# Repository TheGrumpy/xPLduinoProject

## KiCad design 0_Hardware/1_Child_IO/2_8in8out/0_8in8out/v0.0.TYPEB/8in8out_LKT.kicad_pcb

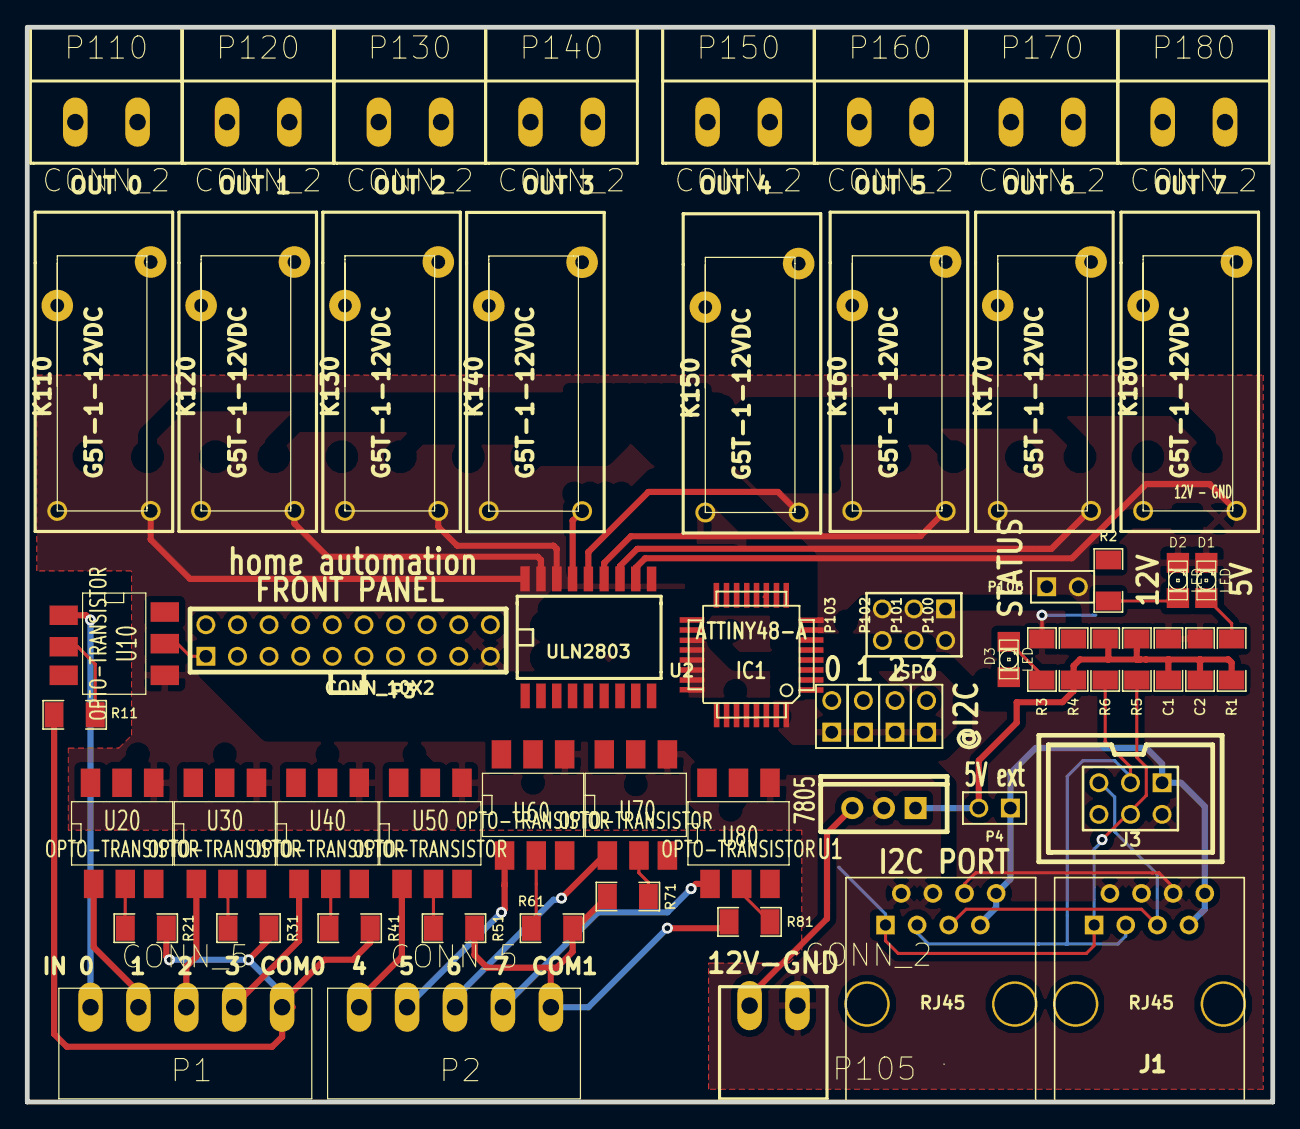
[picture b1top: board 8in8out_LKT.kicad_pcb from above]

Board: 2 copper layers, 100.1 x 86.4 mm, 60 parts (0 on the bottom side), 77 nets.

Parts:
C1, C2: C; SM1206
D1, D2, D3: LED; LED-1206
IC1: ATTINY48-A; TQFP32
ISP0: CONN_3X2; pin_array_3x2
J1, J2: RJ45; RJ45_8
J3: CONN_6; HE10-6
K110, K120, K130, K140, K150, K160, K170, K180: G5T-1-12VDC; LK-T
P1, P2: CONN_5; MOL_CONN_5_MINI
P3: CONN_10X2; pin_array_10x2
P4, P100, P101, P102, P103, P106: CONN_2; PIN_ARRAY_2X1
P105: CONN_2; MOL_CONN_2_MINI
P110, P120, P130, P140, P150, P160, P170, P180: CONN_2; MOL_CONN_2_VH
R1, R3, R11, R21, R31, R41, R51, R61, R71, R81: 2KR; SM1206
R2: 4.7KR; SM1206
R4, R5, R6: 10KR; SM1206
U1: 7805; TO220_7805_VERT
U2: ULN2803; SOIC18
U10, U20, U30, U40, U50, U60, U70, U80: OPTO-TRANSISTOR; CMS-6

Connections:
5V_EXT: J1.7, J1.8, J2.7, J2.8, J3.1, P4.1
+5V: C1.1, C2.1, IC1.4, IC1.18, ISP0.6, P3.20, P4.2, R1.1, R4.1, R5.1, R6.1, U1.VO
+12V: K110.1, K120.1, K130.1, K140.1, K150.1, K160.1, K170.1, K180.1, P105.1, P106.1, R2.1, U1.VI, U2.10
/230_110_1: K110.3, P110.1
/230_110_2: K110.4, P110.2
/230_120_1: K120.3, P120.1
/230_120_2: K120.4, P120.2
/230_130_1: K130.3, P130.1
/230_130_2: K130.4, P130.2
/230_140_1: K140.3, P140.1
/230_140_2: K140.4, P140.2
/230_150_1: K150.3, P150.1
/230_150_2: K150.4, P150.2
/230_160_1: K160.3, P160.1
/230_160_2: K160.4, P160.2
/230_170_1: K170.3, P170.1
/230_170_2: K170.4, P170.2
/230_180_1: K180.3, P180.1
/230_180_2: K180.4, P180.2
/INT: IC1.31, J1.5, J2.5, J3.5
A0: IC1.1, P103.2
A1: IC1.2, P102.2
A2: IC1.3, P101.2
A3: IC1.6, P100.2
CMD0: IC1.30, P3.1, U10.5
CMD1: IC1.26, P3.3, U20.5
CMD2: IC1.25, P3.5, U30.5
CMD3: IC1.24, P3.7, U40.5
CMD4: IC1.23, P3.9, U50.5
CMD5: IC1.22, P3.11, U60.5
CMD6: IC1.20, P3.13, U70.5
CMD7: IC1.19, P3.15, U80.5
COM0: P1.5, R11.2, R21.2, R31.2, R41.2
COM1: P2.5, R51.2, R61.2, R71.2, R81.2
GND: C1.2, C2.2, D1.2, D2.2, IC1.5, IC1.21, ISP0.2, J1.2, J1.4, J1.6, J2.2, J2.4, J2.6, J3.2, P3.19, P100.1, P101.1, P102.1, P103.1, P105.2, P106.2, R3.2, U1.GND, U2.9, U10.4, U20.4, U30.4, U40.4, U50.4, U60.4, U70.4, U80.4
IN0: P1.1, U10.1
IN1: P1.2, U20.1
IN2: P1.3, U30.1
IN3: P1.4, U40.1
IN4: P2.1, U50.1
IN5: P2.2, U60.1
IN6: P2.3, U70.1
IN7: P2.4, U80.1
LED: D3.1, IC1.32, P3.18
MISO: IC1.16, ISP0.5
MOSI: IC1.15, ISP0.4
unnamed: R71.1, U70.2
unnamed: R81.1, U80.2
unnamed: R51.1, U50.2
unnamed: R41.1, U40.2
unnamed: R61.1, U60.2
unnamed: D3.2, R3.1
unnamed: R11.1, U10.2
unnamed: R21.1, U20.2
unnamed: R31.1, U30.2
unnamed: D2.1, R2.2
unnamed: D1.1, R1.2
OUT0: IC1.14, P3.2, U2.1
OUT1: IC1.13, P3.4, U2.2
OUT2: IC1.12, P3.6, U2.3
OUT3: IC1.11, P3.8, U2.4
OUT4: IC1.7, P3.10, U2.5
OUT5: IC1.8, P3.12, U2.6
OUT6: IC1.9, P3.14, U2.7
OUT7: IC1.10, P3.16, U2.8
R0: K110.2, U2.18
R1: K120.2, U2.17
R2: K130.2, U2.16
R3: K140.2, U2.15
R4: K150.2, U2.14
R5: K160.2, U2.13
R6: K170.2, U2.12
R7: K180.2, U2.11
RESET: IC1.29, ISP0.1, P3.17, R4.2
SCK: IC1.17, ISP0.3
SCL: IC1.28, J1.3, J2.3, J3.3, R6.2
SDA: IC1.27, J1.1, J2.1, J3.4, R5.2

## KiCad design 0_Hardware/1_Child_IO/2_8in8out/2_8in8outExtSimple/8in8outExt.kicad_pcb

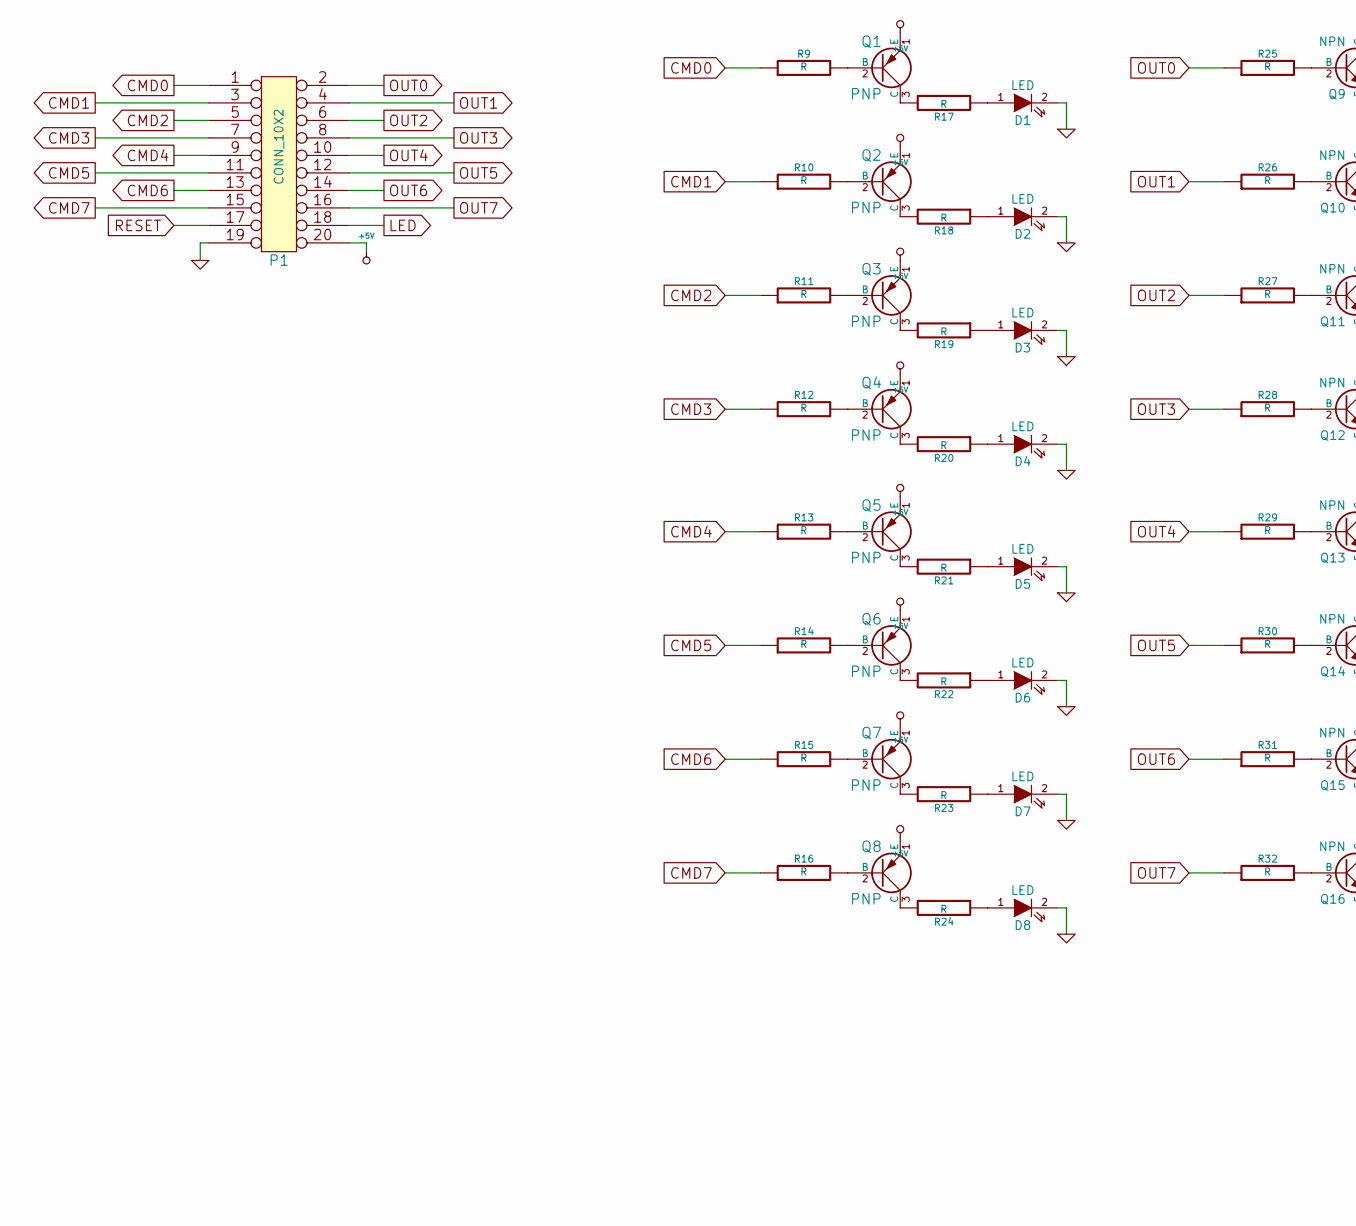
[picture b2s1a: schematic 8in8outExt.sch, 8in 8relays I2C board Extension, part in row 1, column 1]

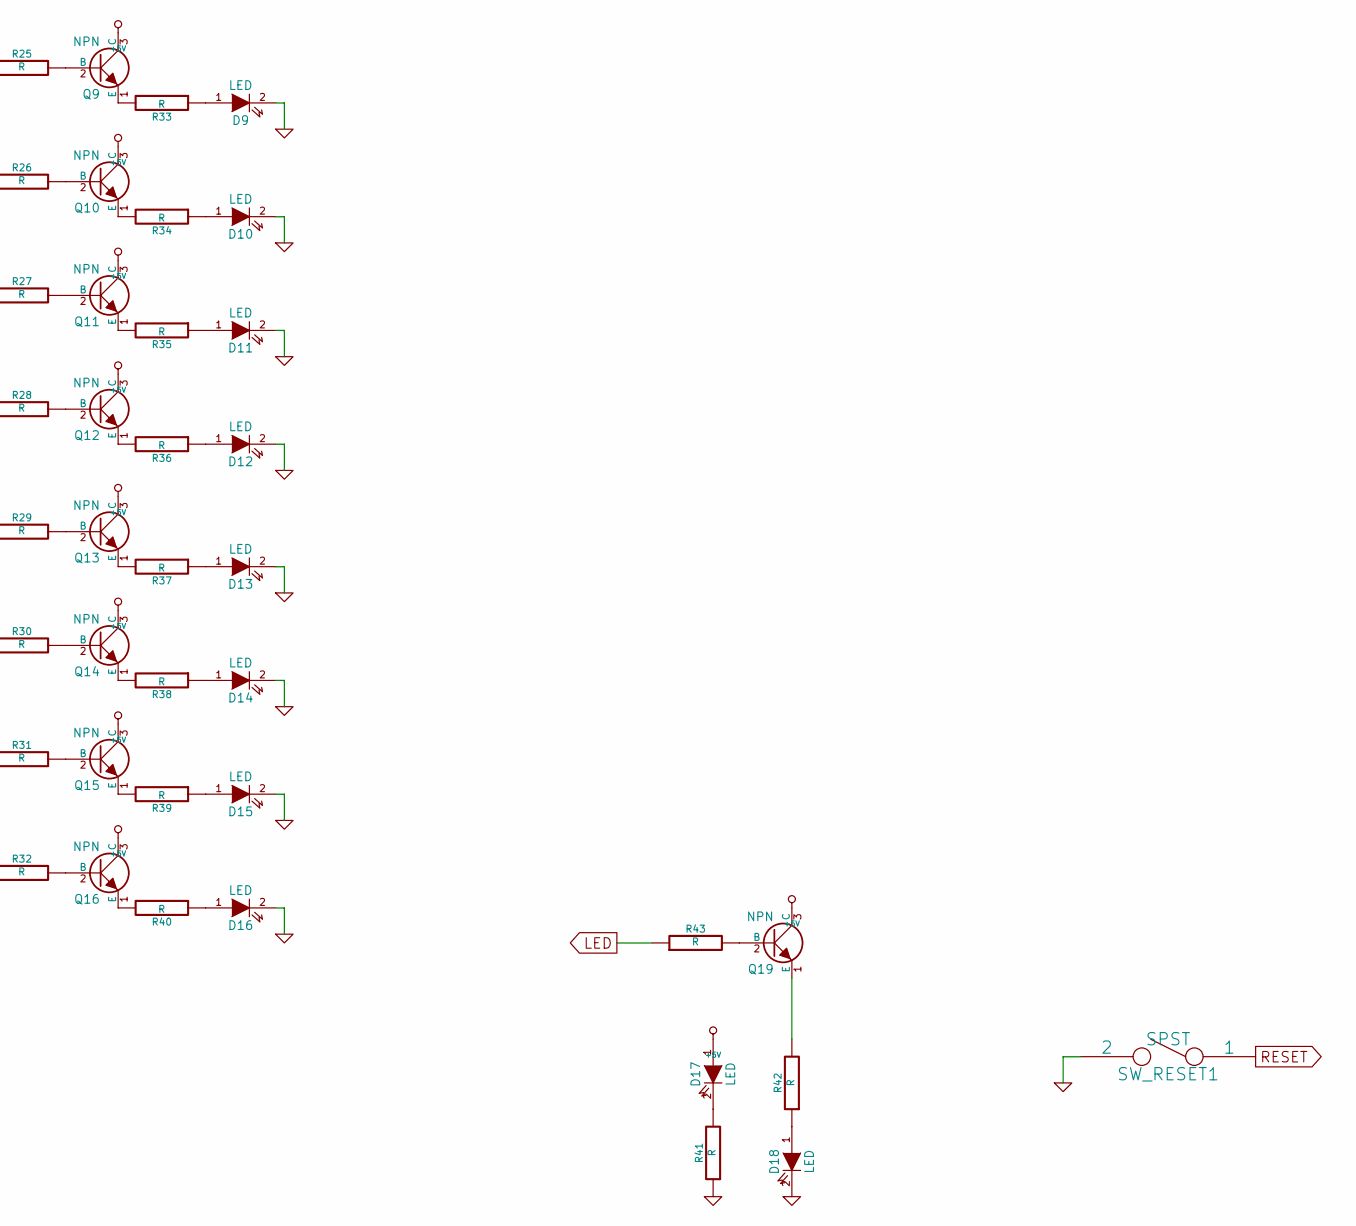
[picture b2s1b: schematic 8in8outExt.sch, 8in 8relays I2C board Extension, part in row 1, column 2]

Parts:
D1, D2, D3, D4, D5, D6, D7, D8, D9, D10, D11, D12, D13, D14, D15, D16, D17, D18: LED
P1: CONN_10X2
Q1, Q2, Q3, Q4, Q5, Q6, Q7, Q8: PNP
Q9, Q10, Q11, Q12, Q13, Q14, Q15, Q16, Q19: NPN
R9, R10, R11, R12, R13, R14, R15, R16, R25, R26, R27, R28, R29, R30, R31, R32, R43: R
R17, R18, R19, R20, R21, R22, R23, R24, R33, R34, R35, R36, R37, R38, R39, R40, R41, R42: R
SW_RESET1: SPST

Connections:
+5V: D17.1 (A), P1.20, Q1.1 (E), Q2.1 (E), Q3.1 (E), Q4.1 (E), Q5.1 (E), Q6.1 (E), Q7.1 (E), Q8.1 (E), Q9.3 (C), Q10.3 (C), Q11.3 (C), Q12.3 (C), Q13.3 (C), Q14.3 (C), Q15.3 (C), Q16.3 (C), Q19.3 (C)
CMD0: P1.1, R9.1
CMD1: P1.3, R10.1
CMD2: P1.5, R11.1
CMD3: P1.7, R12.1
CMD4: P1.9, R13.1
CMD5: P1.11, R14.1
CMD6: P1.13, R15.1
CMD7: P1.15, R16.1
GND: D1.2 (K), D2.2 (K), D3.2 (K), D4.2 (K), D5.2 (K), D6.2 (K), D7.2 (K), D8.2 (K), D9.2 (K), D10.2 (K), D11.2 (K), D12.2 (K), D13.2 (K), D14.2 (K), D15.2 (K), D16.2 (K), D18.2 (K), P1.19, R41.1, SW_RESET1.2
LED: P1.18, R43.1
unnamed: Q9.2 (B), R25.2
unnamed: Q10.1 (E), R34.2
unnamed: D10.1 (A), R34.1
unnamed: Q9.1 (E), R33.2
unnamed: D9.1 (A), R33.1
unnamed: D11.1 (A), R35.1
unnamed: Q11.2 (B), R27.2
unnamed: Q11.1 (E), R35.2
unnamed: Q10.2 (B), R26.2
unnamed: Q7.3 (C), R23.2
unnamed: D7.1 (A), R23.1
unnamed: Q6.2 (B), R14.2
unnamed: Q6.3 (C), R22.2
unnamed: D6.1 (A), R22.1
unnamed: D8.1 (A), R24.1
unnamed: Q8.2 (B), R16.2
unnamed: Q8.3 (C), R24.2
unnamed: Q7.2 (B), R15.2
unnamed: D16.1 (A), R40.1
unnamed: Q15.2 (B), R31.2
unnamed: Q15.1 (E), R39.2
unnamed: D15.1 (A), R39.1
unnamed: Q14.2 (B), R30.2
unnamed: Q14.1 (E), R38.2
unnamed: Q16.1 (E), R40.2
unnamed: Q19.1 (E), R42.2
unnamed: Q19.2 (B), R43.2
unnamed: Q16.2 (B), R32.2
unnamed: D13.1 (A), R37.1
unnamed: Q12.2 (B), R28.2
unnamed: Q12.1 (E), R36.2
unnamed: Q13.1 (E), R37.2
unnamed: D12.1 (A), R36.1
unnamed: D14.1 (A), R38.1
unnamed: Q13.2 (B), R29.2
unnamed: D18.1 (A), R42.1
unnamed: D17.2 (K), R41.2
unnamed: Q1.3 (C), R17.2
unnamed: D1.1 (A), R17.1
unnamed: Q4.3 (C), R20.2
unnamed: D4.1 (A), R20.1
unnamed: Q4.2 (B), R12.2
unnamed: Q3.2 (B), R11.2
unnamed: Q3.3 (C), R19.2
unnamed: Q5.2 (B), R13.2
unnamed: Q5.3 (C), R21.2
unnamed: D3.1 (A), R19.1
unnamed: D5.1 (A), R21.1
unnamed: Q1.2 (B), R9.2
unnamed: Q2.2 (B), R10.2
unnamed: Q2.3 (C), R18.2
unnamed: D2.1 (A), R18.1
OUT0: P1.2, R25.1
OUT1: P1.4, R26.1
OUT2: P1.6, R27.1
OUT3: P1.8, R28.1
OUT4: P1.10, R29.1
OUT5: P1.12, R30.1
OUT6: P1.14, R31.1
OUT7: P1.16, R32.1
RESET: P1.17, SW_RESET1.1

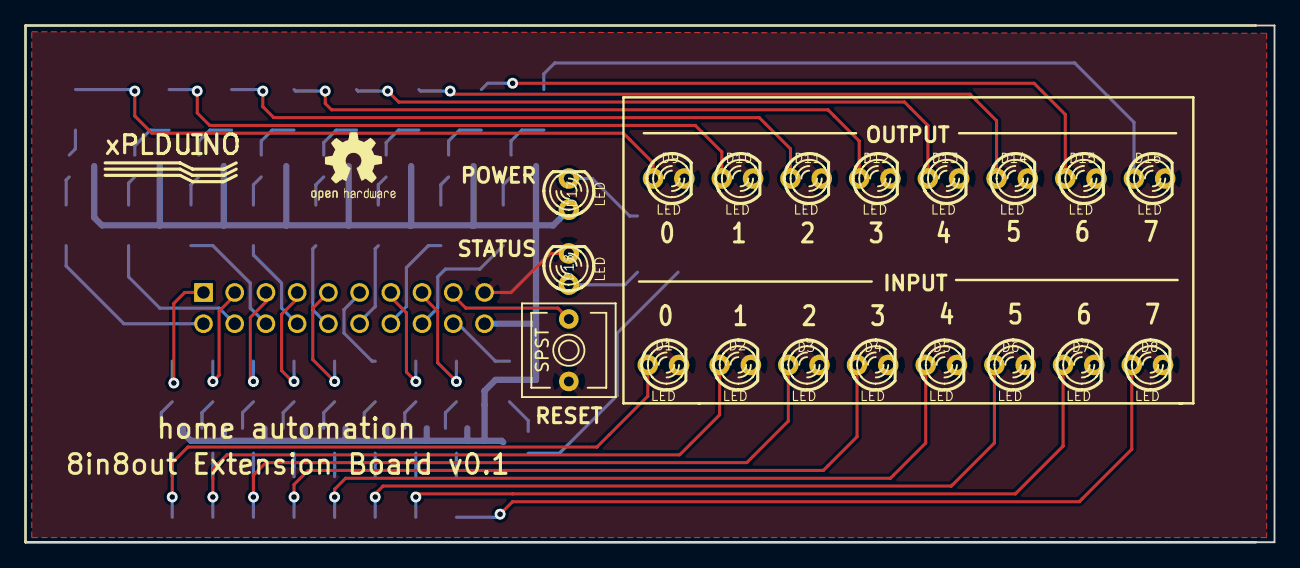
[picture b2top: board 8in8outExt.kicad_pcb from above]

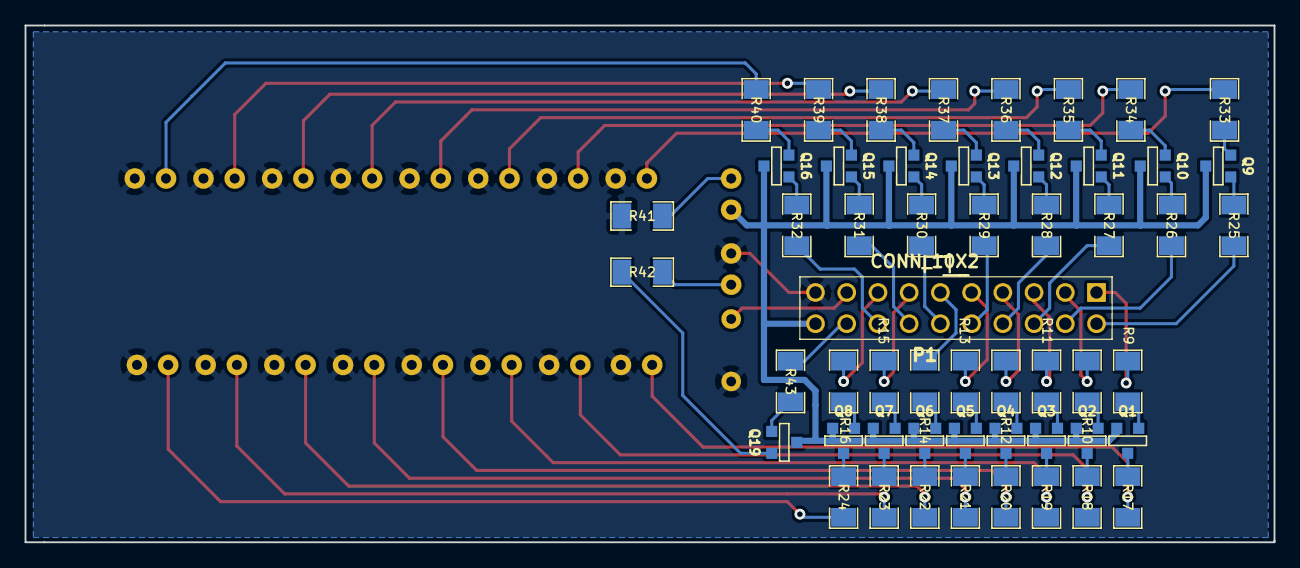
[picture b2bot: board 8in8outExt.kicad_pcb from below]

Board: 2 copper layers, 101.6 x 42.0 mm, 73 parts (53 on the bottom side), 72 nets.

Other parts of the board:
logo_xplduino: VAL**; logo_xplduino

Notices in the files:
0_Hardware/1_Child_IO/2_8in8out/0_8in8out/v0.0.TYPEB/8in8out_LKT.kicad_pcb:
GNU GPL v2
